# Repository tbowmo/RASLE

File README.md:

### NerdClub RASLE board (Rpi Arcade Sound and Light Extension)

This board is an extension board for an arcade cabinet build by the members of Nerdclub.dk, main reason is to be able to make propper shutdown of the arcade cabinet / rpi, and for making easy light control during startup / shutdown sequences.

Features of the board:
* Atmega328 for controlling the board, with the following "peripherals"
 * 3 x 12V PWM channels for LED strips
 * 1 x 5V PWM channel for the onboard FAN
 * header for WS2812B strip (including level converter from 3v3 to 5v)
 * Port for external relay board (for switching mains power)
 * 1 button input routed to the atmeaga328
* RaspberryPI connected things
 * 4 button inputs routed directly to the RPI GPIO header
 * stereo channel I2S 3W class D amplifier (2 x MAX98357)
 * I2C HAT eeprom for configuration

Atmega <-> RPI connections:
* Standard serial port
* SPI / ISP (rpi can reprogram the atmega directly via GPIO)
* I2C HAT eeprom (you could emulate RPI HAT eeprom in the atmega if wanted)
* Reset signal from RPI -> ATmega (disabled via jumper)

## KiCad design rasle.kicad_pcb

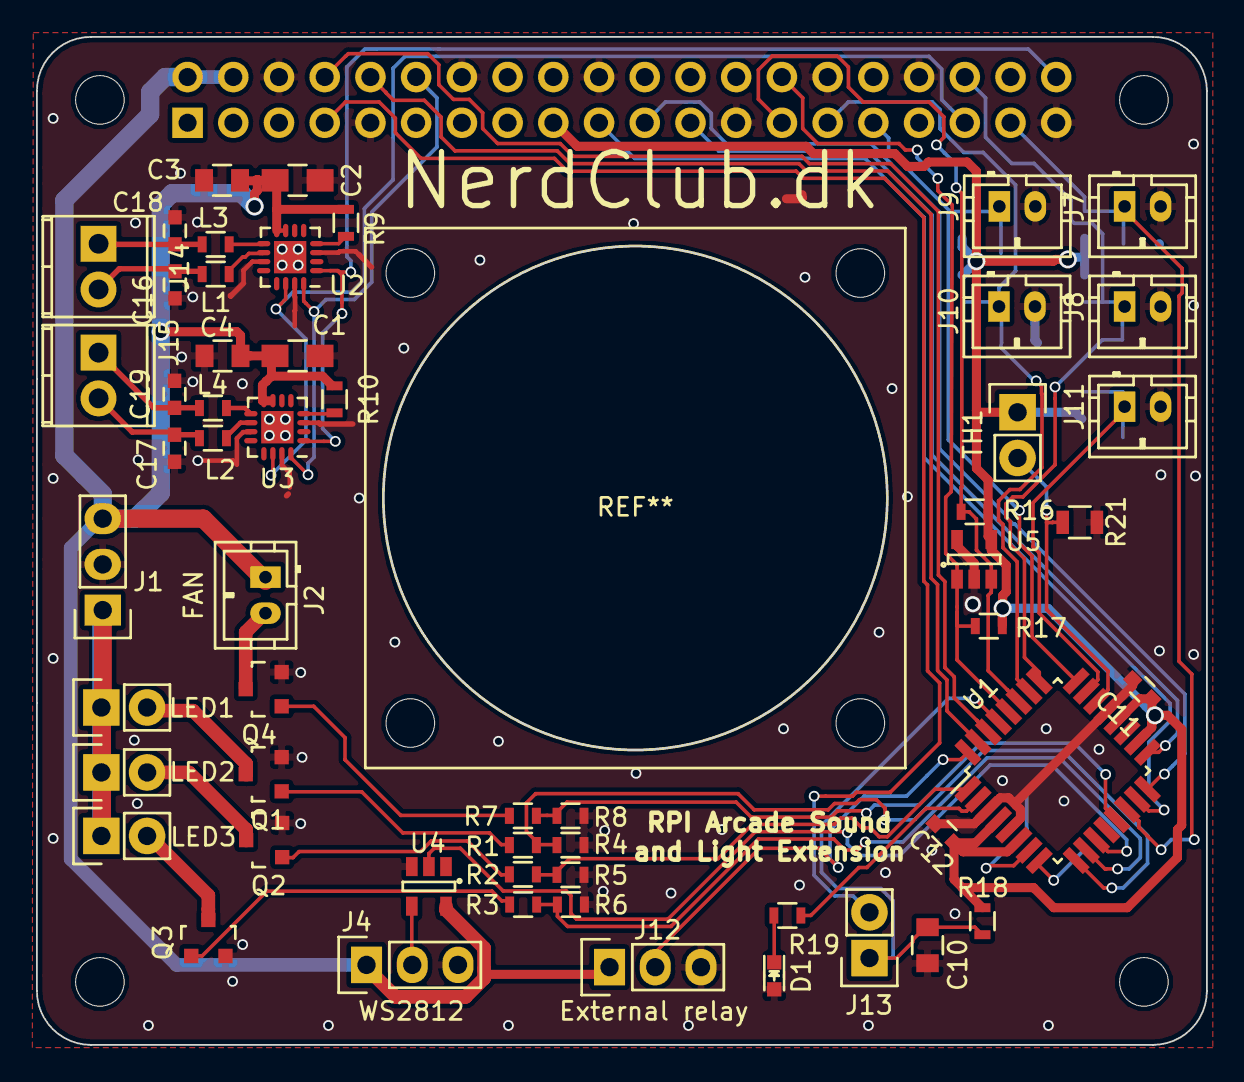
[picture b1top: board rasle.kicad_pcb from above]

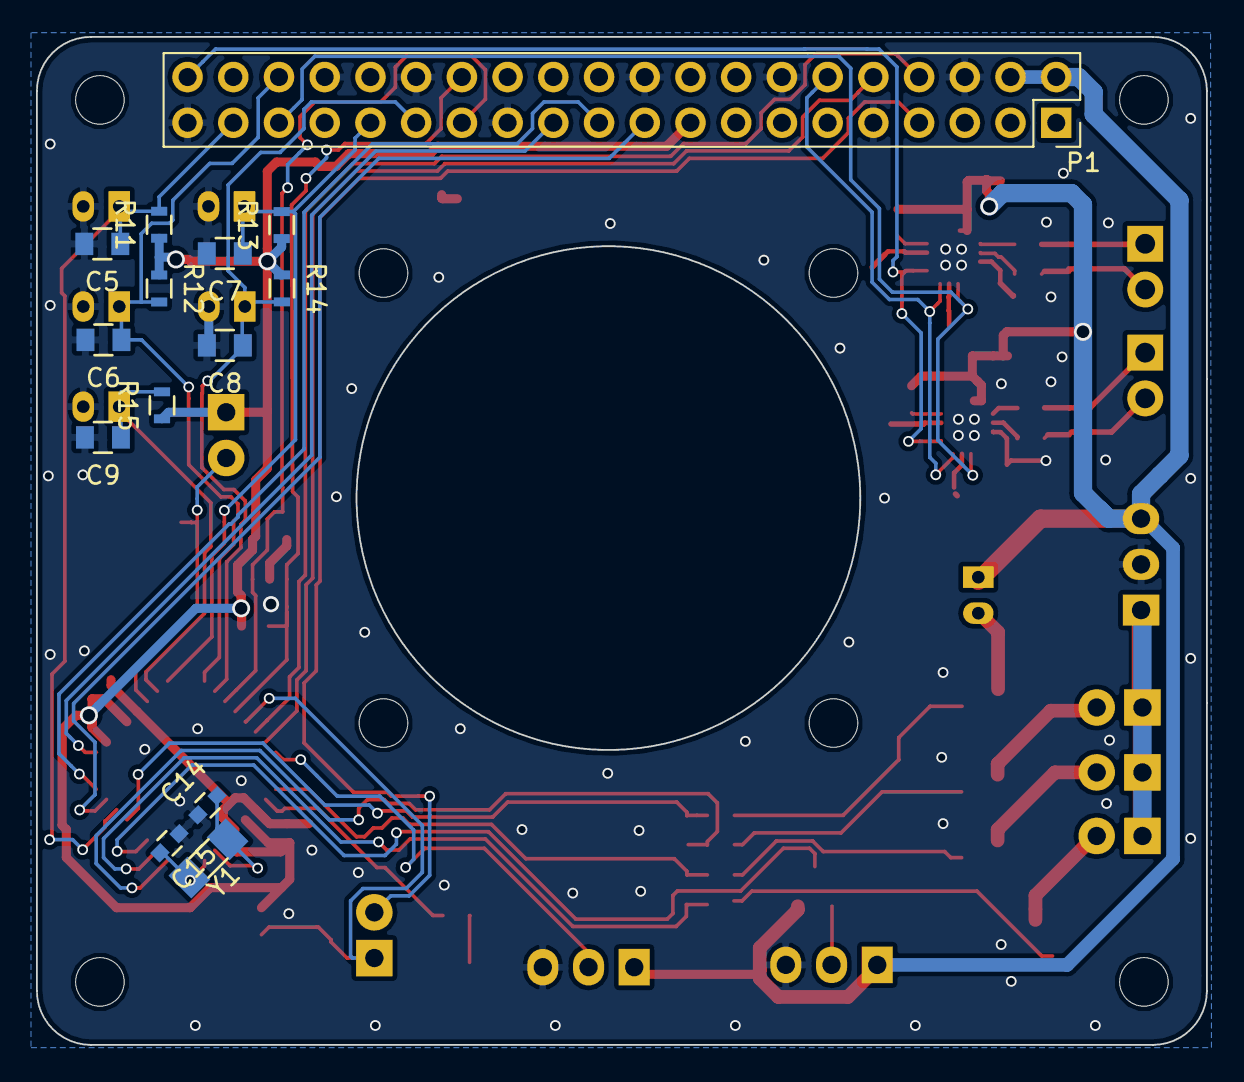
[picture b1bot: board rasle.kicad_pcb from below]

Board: 2 copper layers, 65.0 x 56.0 mm, 74 parts (14 on the bottom side), 51 nets.

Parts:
C1, C2: 10uF; C_0805_HandSoldering
C3, C4, C5, C6, C7, C8, C9, C10: 100nF; C_0805
C11, C12: 100nF; C_0603
C14, C15: 22pF; C_0603
C16, C17, C18, C19: 220nF; C_0603
D1: LED; LED-0603
J1: Power; Pin_Header_Straight_1x03
J2: FAN; Connectors_JST_B2B-PH-K
J4: WS2812; Pin_Header_Straight_1x03
J7: BUTTON1; Connectors_JST_B2B-PH-K
J8: BUTTON2; Connectors_JST_B2B-PH-K
J9: BUTTON3; Connectors_JST_B2B-PH-K
J10: BUTTON4; Connectors_JST_B2B-PH-K
J11: BUTTON_PWR; Connectors_JST_B2B-PH-K
J12: External relay; Pin_Header_Straight_1x03
J13: Reset disable; Pin_Header_Straight_1x02
J14, J15: Conn_01x02_Male; TerminalBlock_Pheonix_MPT-2.54mm_2pol
L1, L2, L3, L4: Ferrite_Bead_Small; R_0603
LED1, LED2, LED3: PWM; Pin_Header_Straight_1x02
MK1, MK2, MK3, MK4: M2.5; MountingHole_2.7mm_M2.5
P1: Conn_02x20_Odd_Even; PinSocket_2x20_P2.54mm_Vertical
Q1, Q2, Q3, Q4: Q_NMOS_GDS; SOT-23
R1, R2, R3, R7: 0R; R_0603
R4, R5, R6, R8, R11, R12, R13, R14, R15, R18: 10k; R_0603
R9, R10: R; R_0603
R16, R17: 4k7; R_0603
R19: 220R; R_0603
R21: 100k; R_0805
TH1: 100k; Pin_Header_Straight_1x02
U1: ATmega328-AU; TQFP-32_7x7mm_Pitch0.8mm
U2, U3: MAX98357; QFN-16-1EP_3x3mm_Pitch0.5mm
U4: 74AUP1G34; SOT-23-5
U5: 24AA02-OT; SOT-23-5
Y1: Crystal; XTAL_3.2x1.5mm

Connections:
+3V3: C11.1, C12.1, P1.1, P1.17, R11.1, R12.1, R13.1, R14.1, R15.1, R16.1, R17.1, R18.2, TH1.1, U1.4, U1.6, U1.18, U1.20, U5.4
+5V: C1.1, C2.1, C3.1, C4.1, J1.3, J2.1, J4.1, J12.1, P1.2, P1.4, R9.1, R10.1, U2.7, U2.8, U3.7, U3.8, U4.5
+12V: J1.1, LED1.1, LED2.1, LED3.1
/BCLK: P1.12, U2.16, U3.16
/BTN_PWR: C9.1, J11.1, R15.2, U1.23
/BUTTON1: C5.1, J7.1, P1.37, R11.2, U1.14
/BUTTON2: C6.1, J8.1, P1.36, R12.2, U1.25
/BUTTON3: C7.1, J9.1, P1.31, R13.2, U1.24
/BUTTON4: C8.1, J10.1, P1.29, R14.2, U1.26
/DIN: P1.40, U2.1, U3.1
/FAN: R7.1, R8.2, U1.13
/GPIO4(GCLK): J13.2, P1.7
/GPIO9(SPI0_MISO): P1.21, U1.16
/GPIO10(SPI0_MOSI): P1.19, U1.15
/GPIO11(SPI0_SCK): P1.23, U1.17
/GPIO14(TXD0): P1.8, U1.30
/GPIO15(RXD0): P1.10, U1.31
/GPIO19(SPI1_MISO): P1.35, U2.14, U3.14
/ID_SC: P1.28, R17.2, U1.28, U5.1
/ID_SD: P1.27, R16.2, U1.27, U5.3
/POWER: J12.2, U1.32
/PWM1: R1.1, R4.2, U1.9
/PWM2: R2.1, R5.2, U1.1
/PWM3: R3.1, R6.2, U1.10
/RESET_ATMEGA: C10.1, J13.1, R18.1, U1.29
/WS2812_DATA: U1.11, U4.2
GND: C1.2, C2.2, C3.2, C4.2, C5.2, C6.2, C7.2, C8.2, C9.2, C10.2, C11.2, C12.2, C14.1, C15.1, C16.2, C17.2, C18.2, C19.2, D1.2, J1.2, J4.3, J7.2, J8.2, J9.2, J10.2, J11.2, J12.3, P1.6, P1.9, P1.14, P1.20, P1.25, P1.30, P1.34, P1.39, Q1.2, Q2.2, Q3.2, Q4.2, R4.1, R5.1, R6.1, R8.1, R21.2, U1.3, U1.5, U1.21, U2.3, U2.11, U2.15, U2.17, U3.3, U3.11, U3.15, U3.17, U4.3, U5.2, U5.5
unnamed: C14.2, U1.7, Y1.1
unnamed: C15.2, U1.8, Y1.2
unnamed: C16.1, J14.2, L1.1
unnamed: C17.1, J15.2, L2.1
unnamed: C18.1, J14.1, L3.1
unnamed: C19.1, J15.1, L4.1
unnamed: D1.1, R19.2
unnamed: J2.2, Q4.3
unnamed: J4.2, U4.4
unnamed: L1.2, U2.10
unnamed: L2.2, U3.10
unnamed: L3.2, U2.9
unnamed: L4.2, U3.9
unnamed: LED1.2, Q1.3
unnamed: LED2.2, Q2.3
unnamed: LED3.2, Q3.3
unnamed: Q1.1, R1.2
unnamed: Q2.1, R2.2
unnamed: Q3.1, R3.2
unnamed: Q4.1, R7.2
unnamed: R9.2, U2.4
unnamed: R10.2, U3.4
unnamed: R19.1, U1.2
unnamed: R21.1, TH1.2, U1.22

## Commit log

2018-10-05 Added manufacturing files
2018-10-05 added license files
2018-10-06 Added EEPROM for HAT compatability
2018-10-08 Added RTC chip for timekeeping
2018-10-10 Removed RTC chip as it is not necessary
2018-10-10 Updated gerbers
2018-10-11 Minor touchup / beautifying of routing
2018-10-12 Connected atmega to all buttons, so it can listen to the same button events as RPI
2019-11-13 PCB manufacturing
